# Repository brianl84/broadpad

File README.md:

# 10-Key QMK Hackpad

A compact 10-key mechanical macropad designed for **daily computer use and live directing/broadcasting**.

The hackpad is powered by a **Seeed Studio XIAO RP2040** and runs **QMK Firmware**. Each key is assigned to a dedicated function key from **F13 to F22**, allowing the macropad to be used with software that supports custom keyboard shortcuts and macros.

## Features

* 10 programmable mechanical keys
* Seeed Studio XIAO RP2040
* QMK Firmware
* F13–F22 key mapping
* Direct GPIO connection for each key
* No keyboard matrix
* No switching diodes
* Compact and portable design
* Designed for daily computer use
* Designed for live directing and broadcasting
* Custom PCB
* Custom case designed in Tinkercad
* USB connection

## Intended Use

This hackpad was designed for **daily computer use** as well as **live directing and broadcasting**.

### Daily Use

The macropad provides ten additional function keys, F13–F22, which can be assigned to custom shortcuts in applications that support them.

This allows frequently used commands to be accessed without occupying the standard F1–F12 function keys.

### Live Directing / Broadcasting

The macropad can also be used as a compact control interface for live production.

For example, F13–F22 can be assigned in broadcasting or production software to functions such as:

* Scene switching
* Start / stop recording
* Audio controls
* Microphone mute
* Media playback
* Stream controls
* Production shortcuts
* Custom macros

The actual actions are assigned by the software being controlled, while the macropad simply sends the corresponding F13–F22 keycodes.

## Hardware

| Component                         | Quantity | Description            |
| --------------------------------- | -------: | ---------------------- |
| Seeed Studio XIAO RP2040          |        1 | Main microcontroller   |
| Cherry MX-style mechanical switch |       10 | User input             |
| MX-compatible keycap              |       10 | Keycaps                |
| Custom PCB                        |        1 | Main circuit board     |
| Custom case                       |        1 | Designed in Tinkercad  |
| USB cable                         |        1 | Connection to computer |

## Electrical Design

This macropad uses a simple **direct GPIO design** instead of a traditional keyboard matrix.

Each mechanical switch is connected directly to an individual GPIO pin on the XIAO RP2040.

Because every switch has its own GPIO connection, switching diodes are not required.

```text
SW1  ── GPIO
SW2  ── GPIO
SW3  ── GPIO
SW4  ── GPIO
SW5  ── GPIO
SW6  ── GPIO
SW7  ── GPIO
SW8  ── GPIO
SW9  ── GPIO
SW10 ── GPIO
```

This keeps the circuit simple and is suitable for a small 10-key macropad.

## Schematic

The schematic was designed in **KiCad**.

It contains the 10 mechanical switches and the XIAO RP2040, with each switch connected directly to an individual GPIO pin.

## PCB

The PCB was designed in **KiCad**.

It contains the 10 mechanical switch footprints, the XIAO RP2040 footprint, mounting features, and the required electrical connections.

## Case Design

The case was designed in **Tinkercad**.

It is designed to hold the PCB, switches, and keycaps while keeping the macropad compact and suitable for desktop use.

The case design also shows how the different components fit together during assembly.

## Completed Hackpad

The completed hackpad is shown below.

## Key Layout

The hackpad contains 10 physical keys mapped to the function keys **F13 through F22**.

| Key | Switch | QMK Keycode |
| --- | ------ | ----------- |
| 1   | SW1    | F13         |
| 2   | SW2    | F14         |
| 3   | SW3    | F15         |
| 4   | SW4    | F16         |
| 5   | SW5    | F17         |
| 6   | SW6    | F18         |
| 7   | SW7    | F19         |
| 8   | SW8    | F20         |
| 9   | SW9    | F21         |
| 10  | SW10   | F22         |

## Firmware

This project uses [QMK Firmware](https://qmk.fm/).

The current keymap assigns the 10 physical switches to F13–F22:

```text
SW1  → F13
SW2  → F14
SW3  → F15
SW4  → F16
SW5  → F17
SW6  → F18
SW7  → F19
SW8  → F20
SW9  → F21
SW10 → F22
```

Using F13–F22 keeps the macropad's controls separate from the standard F1–F12 function keys.

The keys can then be assigned to different functions inside compatible software, such as broadcasting, audio, media, editing, and productivity applications.

## GPIO Connections

Each switch is connected directly to an individual GPIO pin on the XIAO RP2040.

| Key | Switch |    GPIO | QMK Keycode |
| --- | ------ | ------: | ----------- |
| 1   | SW1    | GPIO 11 | F13         |
| 2   | SW2    | GPIO 10 | F14         |
| 3   | SW3    |  GPIO 9 | F15         |
| 4   | SW4    |  GPIO 8 | F16         |
| 5   | SW5    |  GPIO 7 | F17         |
| 6   | SW6    |  GPIO 6 | F18         |
| 7   | SW7    |  GPIO 5 | F19         |
| 8   | SW8    |  GPIO 4 | F20         |
| 9   | SW9    |  GPIO 3 | F21         |
| 10  | SW10   |  GPIO 2 | F22         |

> The GPIO assignments above should match the final QMK firmware configuration.

## Bill of Materials

The following BOM describes the actual hardware used in this project.

| Reference | Quantity | Component                         | Footprint / Notes                                    |
| --------- | -------: | --------------------------------- | ---------------------------------------------------- |
| SW1–SW10  |       10 | Cherry MX-style mechanical switch | `Button_Switch_Keyboard:SW_Cherry_MX_1.00u_PCB`      |
| U1        |        1 | Seeed Studio XIAO RP2040          | `HackclubPad:XIAO-Generic-Hybrid-14P-2.54-21X17.8MM` |
| —         |       10 | MX-compatible keycap              | Mechanical keyboard keycap                           |
| —         |        1 | Custom PCB                        | KiCad-designed                                       |
| —         |        1 | Custom case                       | Tinkercad-designed                                   |
| —         |        1 | USB cable                         | USB connection                                       |

### Electronics

The electronic components used in this project are:

* **1 × Seeed Studio XIAO RP2040**
* **10 × Cherry MX-style mechanical switches**

The switches are connected directly to individual GPIO pins.

No keyboard matrix is used, so no switching diodes are required.

### Mechanical Parts

The mechanical components are:

* **10 × MX-compatible keycaps**
* **1 × custom PCB**
* **1 × custom case**
* Screws or mounting hardware as required by the case design

## Design Goals

The main goal of this project is to create a small and practical macropad that can be used every day while also providing dedicated controls for live production.

The 10-key layout keeps the device compact while providing ten additional function keys that can be assigned to frequently used shortcuts and broadcasting functions.

The direct GPIO design keeps the electrical circuit simple and avoids the additional components required by a traditional keyboard matrix.

## Future Improvements

Possible future improvements include:

* RGB lighting
* Rotary encoder
* OLED display
* Additional QMK layers
* More advanced macros
* Dedicated broadcasting profiles
* Custom keycap legends
* Improved case design

## License

This project is open source. See the repository license for details.

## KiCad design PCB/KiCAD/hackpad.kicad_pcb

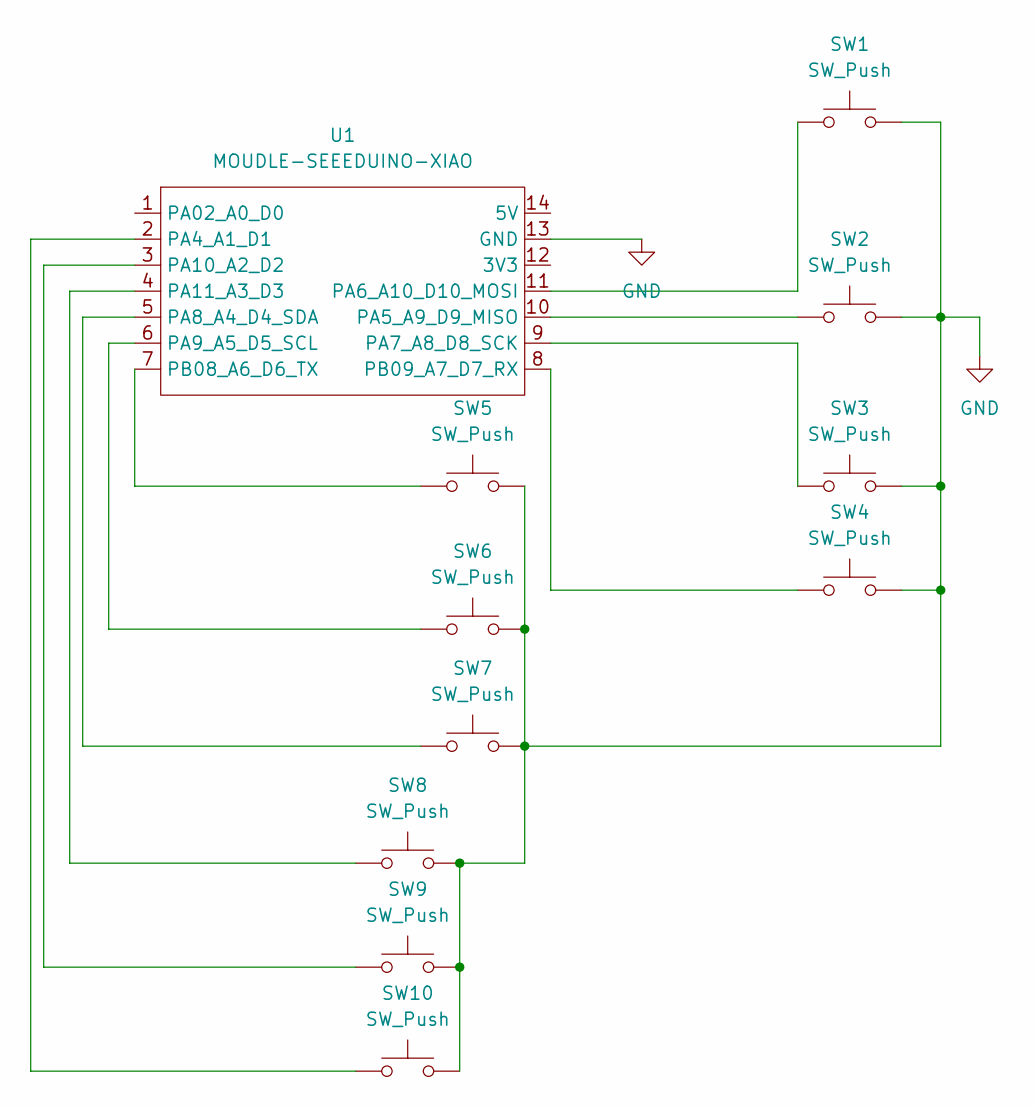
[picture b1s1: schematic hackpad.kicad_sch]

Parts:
SW1, SW2, SW3, SW4, SW5, SW6, SW7, SW8, SW9, SW10: SW_Push; SW_Cherry_MX_1.00u_PCB
U1: MOUDLE-SEEEDUINO-XIAO; XIAO-Generic-Hybrid-14P-2.54-21X17.8MM

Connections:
GND: SW1.2, SW2.2, SW3.2, SW4.2, SW5.2, SW6.2, SW7.2, SW8.2, SW9.2, SW10.2, U1.13 (GND)
unnamed: SW10.1, U1.2 (PA4_A1_D1)
unnamed: SW2.1, U1.10 (PA5_A9_D9_MISO)
unnamed: SW1.1, U1.11 (PA6_A10_D10_MOSI)
unnamed: SW3.1, U1.9 (PA7_A8_D8_SCK)
unnamed: SW7.1, U1.5 (PA8_A4_D4_SDA)
unnamed: SW6.1, U1.6 (PA9_A5_D5_SCL)
unnamed: SW9.1, U1.3 (PA10_A2_D2)
unnamed: SW8.1, U1.4 (PA11_A3_D3)
unnamed: SW5.1, U1.7 (PB08_A6_D6_TX)
unnamed: SW4.1, U1.8 (PB09_A7_D7_RX)

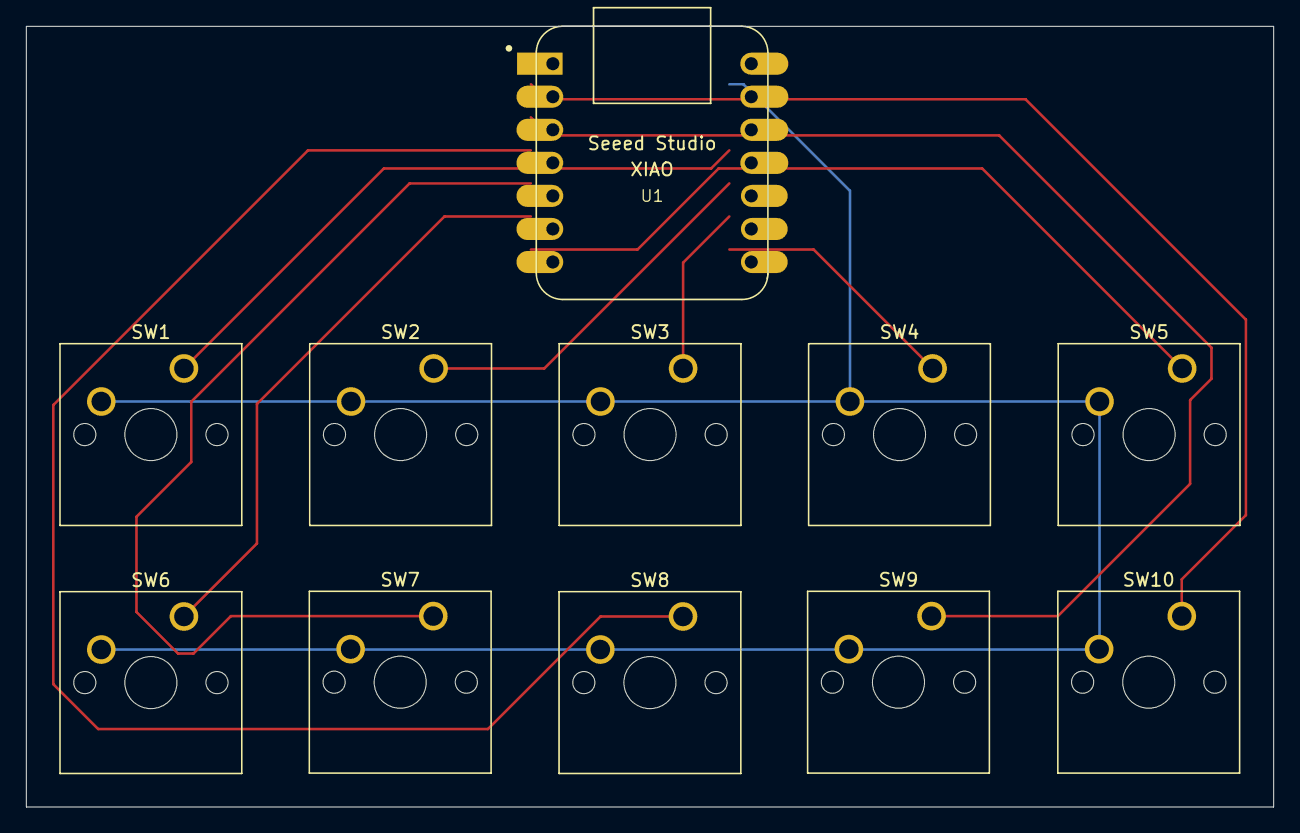
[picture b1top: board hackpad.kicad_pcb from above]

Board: 2 copper layers, 95.8 x 60.0 mm, 11 parts (0 on the bottom side), 11 nets.

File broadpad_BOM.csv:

"Reference","Qty","Value","DNP","Exclude from BOM","Exclude from Board","Footprint","Datasheet"
"SW1,SW2,SW3,SW4,SW5,SW6,SW7,SW8,SW9,SW10","10","SW_Push","","","","Button_Switch_Keyboard:SW_Cherry_MX_1.00u_PCB","~"
"U1","1","MOUDLE-SEEEDUINO-XIAO","","","","HackclubPad:XIAO-Generic-Hybrid-14P-2.54-21X17.8MM",""
